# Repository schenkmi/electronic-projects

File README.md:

# electronic-projects
misc electronic projects

# History

## 2026.09.19

### pre-amp-ECC86/kicad/psu-v6
Large PCB PSU for ECC86 with high side switch. Support LT3080 and LM317. Fix Drain/Source.

## 2026.09.02

### pre-amp-ECC86/kicad/psu-v5
Large PCB PSU for ECC86 with high side switch. Support LT3080 and LM317

## 2026.08.26

### pre-amp-ECC86/kicad/psu-v4
Large PCB PSU for ECC86 without relais. Support LT3080 and LM317

## 2026.08.23

### input-sel-attenuator/software/v9
Power up timer to 64ms wait till voltage is stabilized

## 2026.08.10

### pre-amp-ECC86/kicad/psu-v3
Large PCB PSU for ECC86

## 2026.08.01

### pre-amp-ECC86/kicad/psu-v2
Shrinked and optimized PSU for ECC86

## 2026.07.22

### pre-amp-ECC86/kicad/psu-v1
First version of PSU for ECC86 

## 2026.07.12

### pre-amp-ECC86/kicad/v1
First version of ECC86 based pre-amplifier

### spdif-recv-ak4118-ak4137/software/spdif-recv-ak4118-ak4137-v4.X
Updated software for V4 PCB

## 2026.06.05

### dac-pcm1702-v1/kicad-psu-v8/
DC/DC for +5V digital path

### dac-pcm1702-v1/kicad-asrc-v14
PCB LED fix
External LED support

### spdif-recv-ak4118-ak4137/kicad/v4
External LED support
Change one LDO to TLV1117-3.3 due to power dissipation

## 2026.05.28

### dac-pcm1702-v1/kicad-asrc-v13
PCB re-design with fixed LED ordering

## 2026.05.27

### pre-amp-26A7/ltspice/v2/
New CCS simulation with smaller FETs

## 2026.05.26

### dac-pcm1702-v1/software/spdif-recv-asrc-4392-v12.X
New software for SPDIF ASRC receiver including UART and IR

## 2026.05.16

### dac-pcm1702-v1/kicad-asrc-v12
PSU re-design, UART for debugging, I2C debugging, IR

### spdif-recv-ak4118-ak4137/kicad/v3
Add IR support

## 2026.05.10

### spdif-recv-cs8416-ak4137/kicad/v7
Improved power supply, I2S debug, Serial console

### spdif-recv-ak4118-ak4137/kicad/v2
Small redesign

## 2026.04.25

### spdif-recv-ak4118-ak4137/kicad/v1
Finalize and ordered

### pre-amp-26A7/kicad/v2
Finalize and ordered

## 2026.03.29

### pre-amp-26A7/kicad/v1
Finalize and ordered v1

## 2026.03.28

### lv-psu-dcdc/kicad/fixed-v3
Better thermal management for DC/DC

### lv-lownoise-psu/kicad/v7-dcdc-large-cap
Better thermal handling on DC/DC

### input-sel-attenuator/kicad/v9-10k-47k
Changed footprint for L1 and C1

## 2026.03.11

### lv-psu-dcdc/kicad/fixed-v2
Eval board with different inductors

### hv-psu-discrete/kicad/maida-lt3080-v5
HV PSU with DC/DC for +5V output

## 2026.03.05

### lv-lownoise-psu/kicad/v6-dcdc-large-cap
Finalize v6 with large reservoir cap

## 2026.02.25

### hv-psu-discrete/kicad/maida-lt3080-v5-26A7GT
HV PSU for 26A7 pre-amp

## 2026.01.13

### input-sel-attenuator/software/ir-debug-v3
Update MCC generated code

### dac-pcm1792a/software/asrc-pcm1792a-v4.X
Update MCC generated code

### dac-pcm1702-v1/software/v8
Update MCC generated code

### spdif-recv-cs8416-ak4137/software/spdif-recv-cs8416-ak4137-v5.X
Update MCC generated code

### input-sel-attenuator/software/v9
Update MCC generated code

### rpi-hat-spdif/kicad/V9
RPI HAT SPDIF Output increase hole diameter to 3.2mm

### rpi-hat-spdif/kicad/V9-min
RPI HAT SPDIF Output minized PCB increase hole diameter to 3.2mm

## 2026.01.01

### adapter/spdif/kicad/v2
LVDS SPDIF XMIT with rotated connector 

### adapter/spdif/kicad/v2b
LVDS SPDIF XMIT with standard connector 

### rpi-hat-spdif/kicad/V7-min
RPI HAT SPDIF Output minized PCB

### rpi-hat-spdif/kicad/V8
RPI HAT SPDIF Output new PCB

## 2025.12.20

### adapter/spdif/kicad/v1
Finalize v1 LVDS SPDIF XMIT

### rpi-hat-spdif/kicad/v6
RPI HAT SPDIF Output

### rpi-hat-spdif/kicad/v6-min
RPI HAT SPDIF Output minimized

## 2025.12.08

### pre-amp-ECC88/kicad/v9
Finalize and ordered v9

## 2025.09.29

### retro/c64-user-port-led
Finalize v1 of C64 user port LED

## 2025.09.28

### dac-pcm1704/kicad/dac-df1706-pcm1704-v2
Finalize and ordered v2

## 2025.09.21

### dac-pcm1704/kicad/dac-pcm1704-v5
Finalize and ordered v5

### dac-pcm1702-v1/kicad-i2s-nos-v7
Finalize and ordered v7

### dac-pcm1792a/kicad/v6/
Finalize and ordered v6

## 2025.09.13

### input-sel-attenuator/software/ir-debug-v2

### input-sel-attenuator/software/v8
V2.5 2025.09.12 Shiny new push button and saving handling
     Use volume when doing channel switch.

## 2025.09.07

### lv-lownoise-psu/kicad/v5-dcdc
Finalize and ordered v5

### lv-lownoise-psu/kicad/v5-dcdc-large-cap
Finalize and ordered v5 with large reservoir cap

## 2025.08.25

### lt1115-phono-mm-mc/kicad/v6
Finalize and ordered v6

## 2025.08.23

### dac-pcm1702-v1/kicad-psu-v7
Finalize and ordered v7

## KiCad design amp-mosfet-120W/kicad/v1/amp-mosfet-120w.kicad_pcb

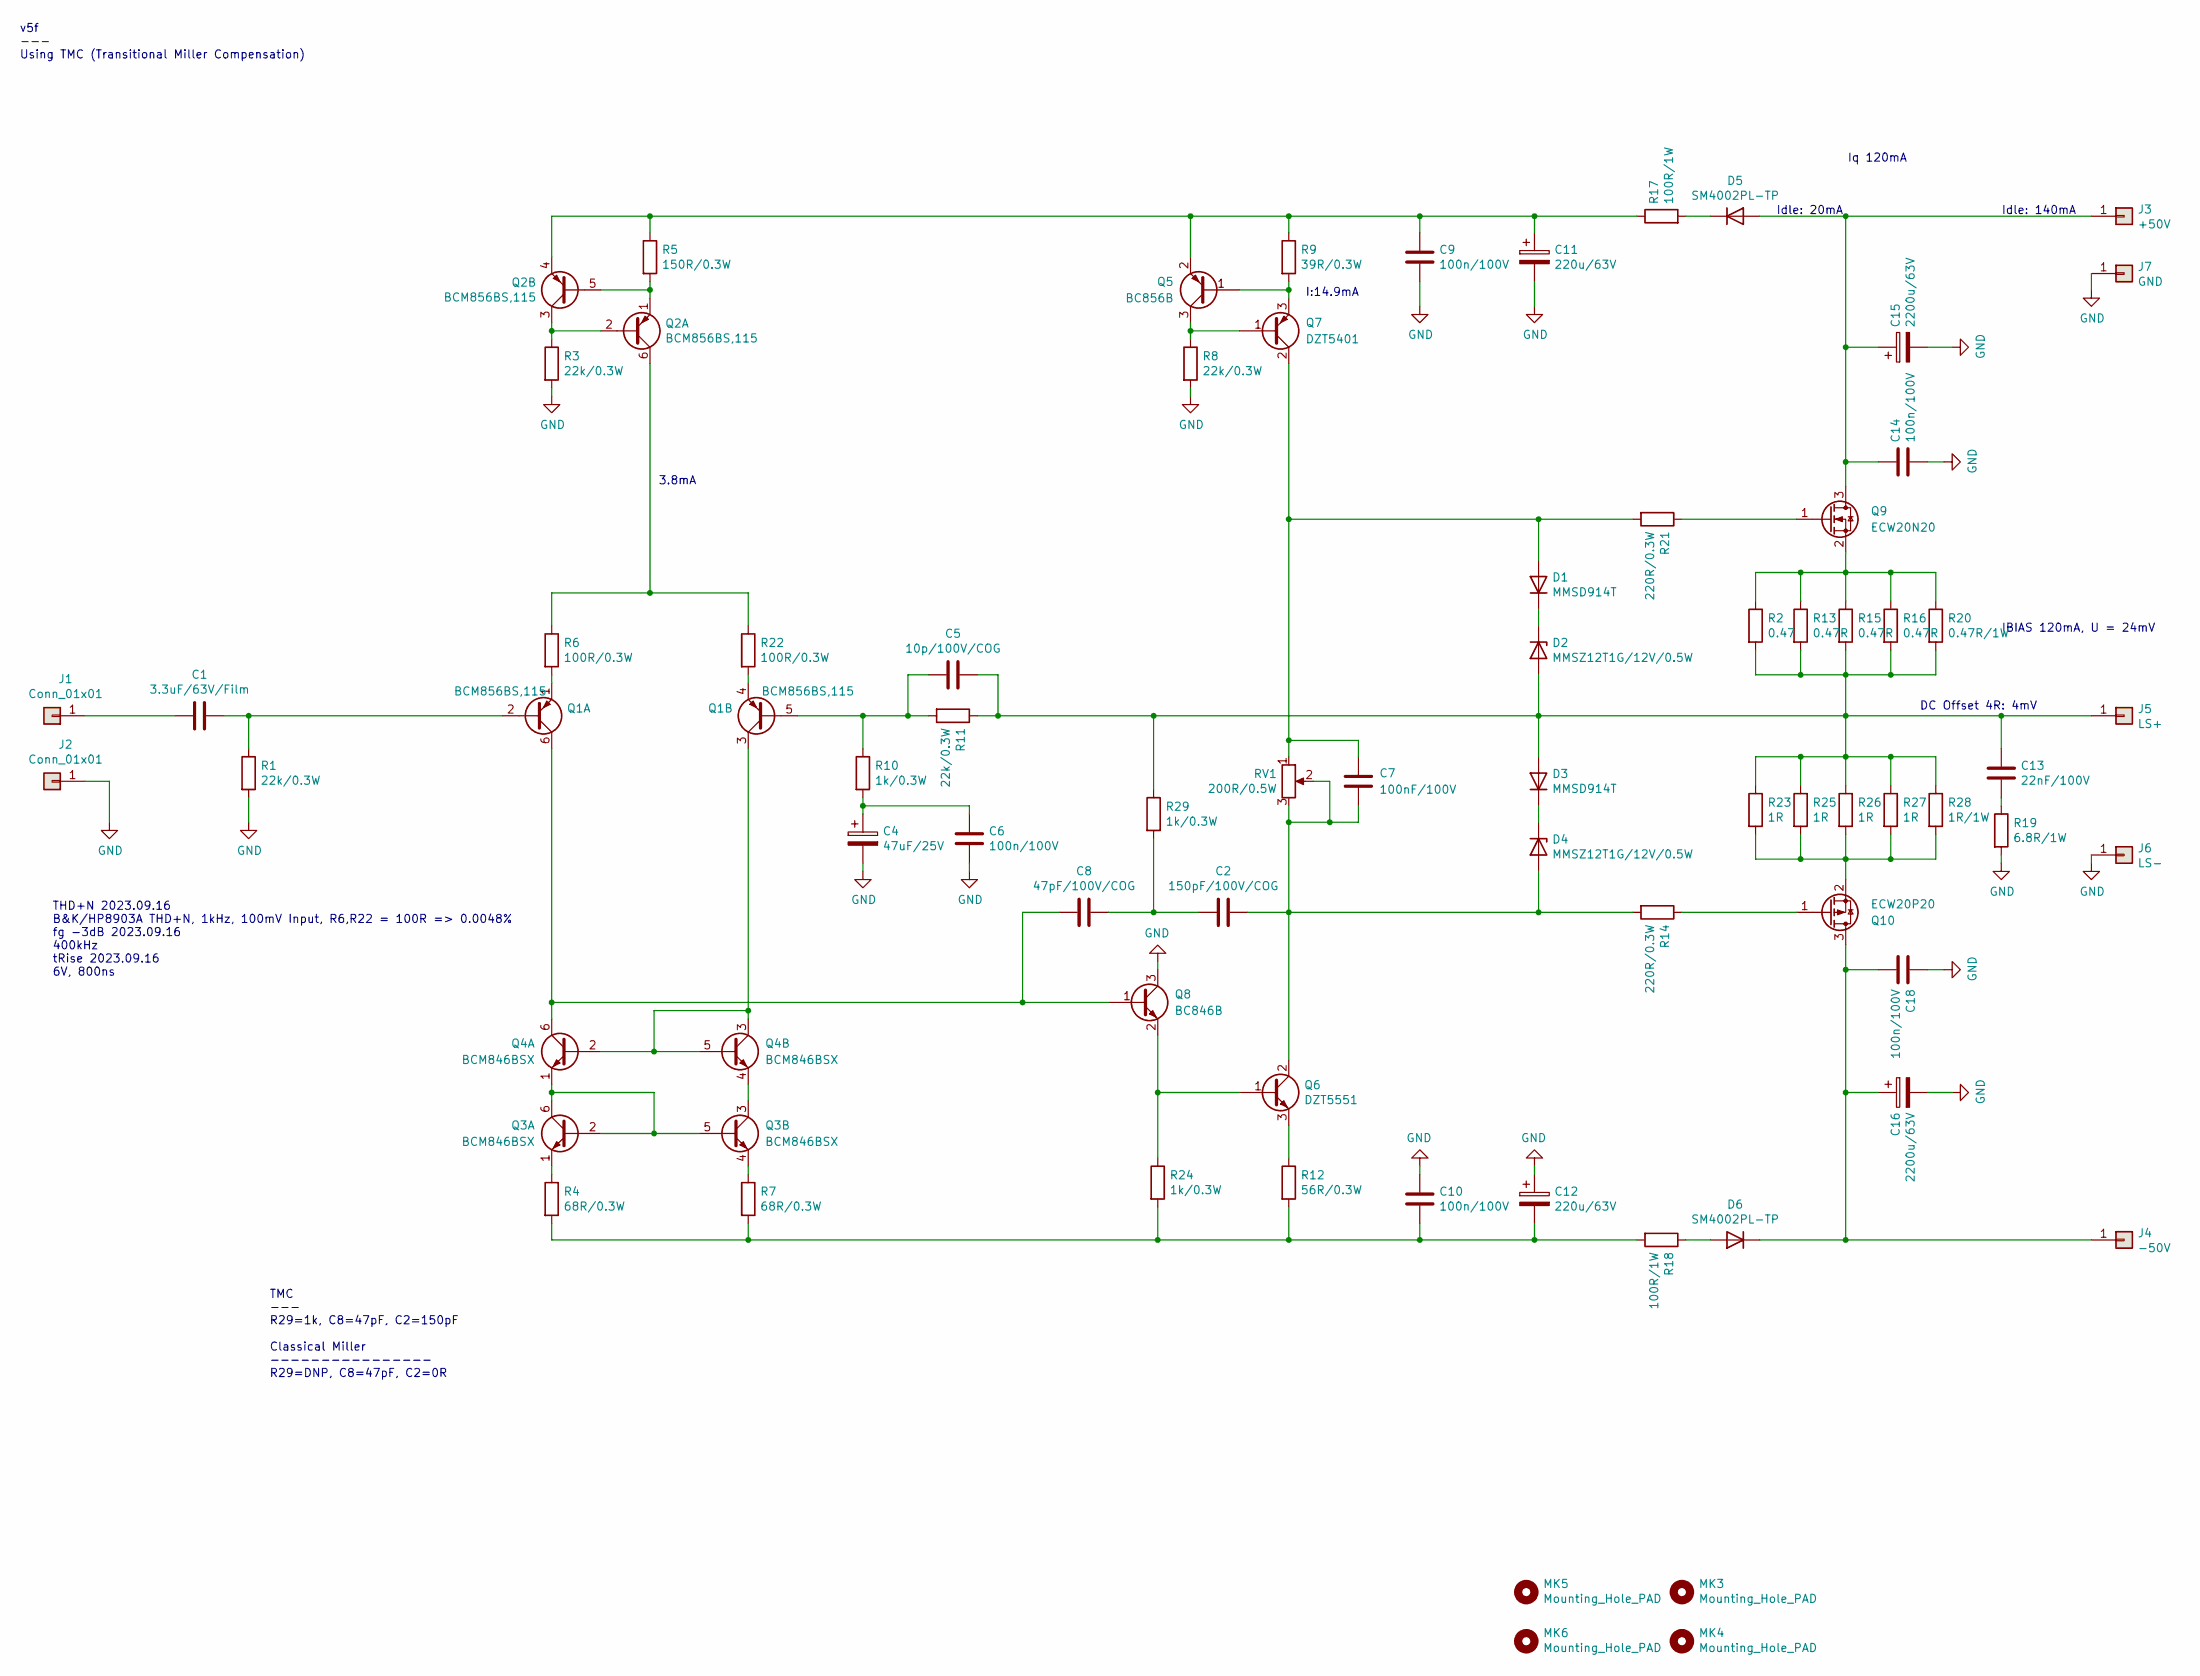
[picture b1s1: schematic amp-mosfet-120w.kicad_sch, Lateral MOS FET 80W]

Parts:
C1: 3.3uF/63V/Film; C_Rect_L7.2mm_W7.2mm_P5.00mm_FKS2_FKP2_MKS2_MKP2
C2: 150pF/100V/COG; C_0805_2012Metric_Pad1.18x1.45mm_HandSolder
C4: 47uF/25V; CP_Radial_D5.0mm_P2.00mm
C5: 10p/100V/COG; C_0805_2012Metric_Pad1.18x1.45mm_HandSolder
C6, C9, C10: 100n/100V; C_Rect_L7.2mm_W2.5mm_P5.00mm_FKS2_FKP2_MKS2_MKP2
C7: 100nF/100V; C_Rect_L7.2mm_W2.5mm_P5.00mm_FKS2_FKP2_MKS2_MKP2
C8: 47pF/100V/COG; C_0805_2012Metric_Pad1.18x1.45mm_HandSolder
C11, C12: 220u/63V; CP_Radial_D12.5mm_P5.00mm
C13: 22nF/100V; C_Rect_L7.2mm_W2.5mm_P5.00mm_FKS2_FKP2_MKS2_MKP2
C14, C18: 100n/100V; C_1206_3216Metric_Pad1.33x1.80mm_HandSolder
C15, C16: 2200u/63V; CP_Radial_D18.0mm_P7.50mm
D1, D3: MMSD914T; D_SOD-123
D2, D4: MMSZ12T1G/12V/0.5W; D_SOD-123
D5, D6: SM4002PL-TP; D_SOD-123F
J1, J2: Conn_01x01; Pin_D1.0mm_L10.0mm
J3: +50V; TE-726386-2_Pitch5.08mm_Drill1.3mm
J4: -50V; TE-726386-2_Pitch5.08mm_Drill1.3mm
J5: LS+; TE-726386-2_Pitch5.08mm_Drill1.3mm
J6: LS-; TE-726386-2_Pitch5.08mm_Drill1.3mm
J7: GND; TE-726386-2_Pitch5.08mm_Drill1.3mm
MK3, MK4: Mounting_Hole_PAD; MountingHole_3.2mm_M3_Pad_Via
MK5, MK6: Mounting_Hole_PAD; MountingHole_3.2mm_M3
Q1, Q2: BCM856BS,115; SOT-363_SC-70-6
Q3, Q4: BCM846BSX; SOT-363_SC-70-6
Q5: BC856B; SOT-23
Q6: DZT5551; SOT-223-3_TabPin2
Q7: DZT5401; SOT-223-3_TabPin2
Q8: BC846B; SOT-23
Q9: ECW20N20; TO-264-3_Horizontal_TabDown
Q10: ECW20P20; TO-264-3_Horizontal_TabDown
R1, R3, R8, R11: 22k/0.3W; R_0805_2012Metric_Pad1.20x1.40mm_HandSolder
R2: 0.47; R_MELF_MMB-0207
R4, R7: 68R/0.3W; R_0805_2012Metric_Pad1.20x1.40mm_HandSolder
R5: 150R/0.3W; R_0805_2012Metric_Pad1.20x1.40mm_HandSolder
R6, R22: 100R/0.3W; R_0805_2012Metric_Pad1.20x1.40mm_HandSolder
R9: 39R/0.3W; R_0805_2012Metric_Pad1.20x1.40mm_HandSolder
R10, R24, R29: 1k/0.3W; R_0805_2012Metric_Pad1.20x1.40mm_HandSolder
R12: 56R/0.3W; R_0805_2012Metric_Pad1.20x1.40mm_HandSolder
R13, R15, R16: 0.47R; R_MELF_MMB-0207
R14, R21: 220R/0.3W; R_0805_2012Metric_Pad1.20x1.40mm_HandSolder
R17, R18: 100R/1W; R_MELF_MMB-0207
R19: 6.8R/1W; R_MELF_MMB-0207
R20: 0.47R/1W; R_MELF_MMB-0207
R23, R25, R26, R27: 1R; R_MELF_MMB-0207
R28: 1R/1W; R_MELF_MMB-0207
RV1: 200R/0.5W; Potentiometer_Bourns_3296W_Vertical

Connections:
GND: C4.2, C6.2, C9.2, C10.1, C11.2, C12.1, C14.2, C15.2, C16.2, C18.1, J2.1 (Pin_1_1), J6.1 (Pin_1_1), J7.1 (Pin_1_1), Q8.3 (C), R1.2, R3.2, R8.2, R19.2
unnamed: C2.2, C8.1, R29.2
unnamed: C4.1, C6.1, R10.2
unnamed: C10.2, C12.2, R4.2, R7.2, R12.2, R18.2, R24.2
unnamed: C13.2, R19.1
unnamed: C7.2, D1.2 (A), Q7.2 (C), R21.2, RV1.1
unnamed: D1.1 (K), D2.1 (K)
unnamed: C5.1, C13.1, D2.2 (A), D3.2 (A), J5.1 (Pin_1_1), R2.2, R11.1, R13.2, R15.2, R16.2, R20.2, R23.1, R25.1, R26.1, R27.1, R28.1, R29.1
unnamed: D3.1 (K), D4.1 (K)
unnamed: C2.1, C7.1, D4.2 (A), Q6.2 (C), R14.2, RV1.2, RV1.3
unnamed: C14.1, C15.1, D5.2 (A), J3.1 (Pin_1_1), Q9.3 (D)
unnamed: D5.1 (K), R17.2
unnamed: D6.2 (A), R18.1
unnamed: C16.1, C18.2, D6.1 (K), J4.1 (Pin_1_1), Q10.3 (D)
unnamed: C1.2, J1.1 (Pin_1_1)
unnamed: C1.1, Q1.2 (B1), R1.1
unnamed: C8.2, Q1.6 (C1), Q4.6 (C1), Q8.1 (B)
unnamed: Q1.1 (E1), R6.2
unnamed: C5.2, Q1.5 (B2), R10.1, R11.2
unnamed: Q1.3 (C2), Q4.2 (B1), Q4.3 (C2), Q4.5 (B2)
unnamed: Q1.4 (E2), R22.2
unnamed: Q2.2 (B1), Q2.3 (C2), R3.1
unnamed: Q2.6 (C1), R6.1, R22.1
unnamed: Q2.1 (E1), Q2.5 (B2), R5.2
unnamed: C9.1, C11.1, Q2.4 (E2), Q5.2 (E), R5.1, R9.1, R17.1
unnamed: Q3.2 (B1), Q3.5 (B2), Q3.6 (C1), Q4.1 (E1)
unnamed: Q3.1 (E1), R4.1
unnamed: Q3.3 (C2), Q4.4 (E2)
unnamed: Q3.4 (E2), R7.1
unnamed: Q5.1 (B), Q7.3 (E), R9.2
unnamed: Q5.3 (C), Q7.1 (B), R8.1
unnamed: Q6.1 (B), Q8.2 (E), R24.1
unnamed: Q6.3 (E), R12.1
unnamed: Q9.1 (G), R21.1
unnamed: Q9.2 (S), R2.1, R13.1, R15.1, R16.1, R20.1
unnamed: Q10.1 (G), R14.1
unnamed: Q10.2 (S), R23.2, R25.2, R26.2, R27.2, R28.2

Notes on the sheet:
THD+N 2023.09.16 B&K/HP8903A THD+N, 1kHz, 100mV Input, R6,R22 = 100R => 0.0048% fg -3dB 2023.09.16 400kHz tRise 2023.09.16 6V, 800ns
TMC --- R29=1k, C8=47pF, C2=150pF Classical Miller ---------------- R29=DNP, C8=47pF, C2=0R
Iq 120mA
Idle: 20mA
v5f --- Using TMC (Transitional Miller Compensation)
Idle: 140mA
DC Offset 4R: 4mV
3.8mA
I:14.9mA
IBIAS 120mA, U = 24mV

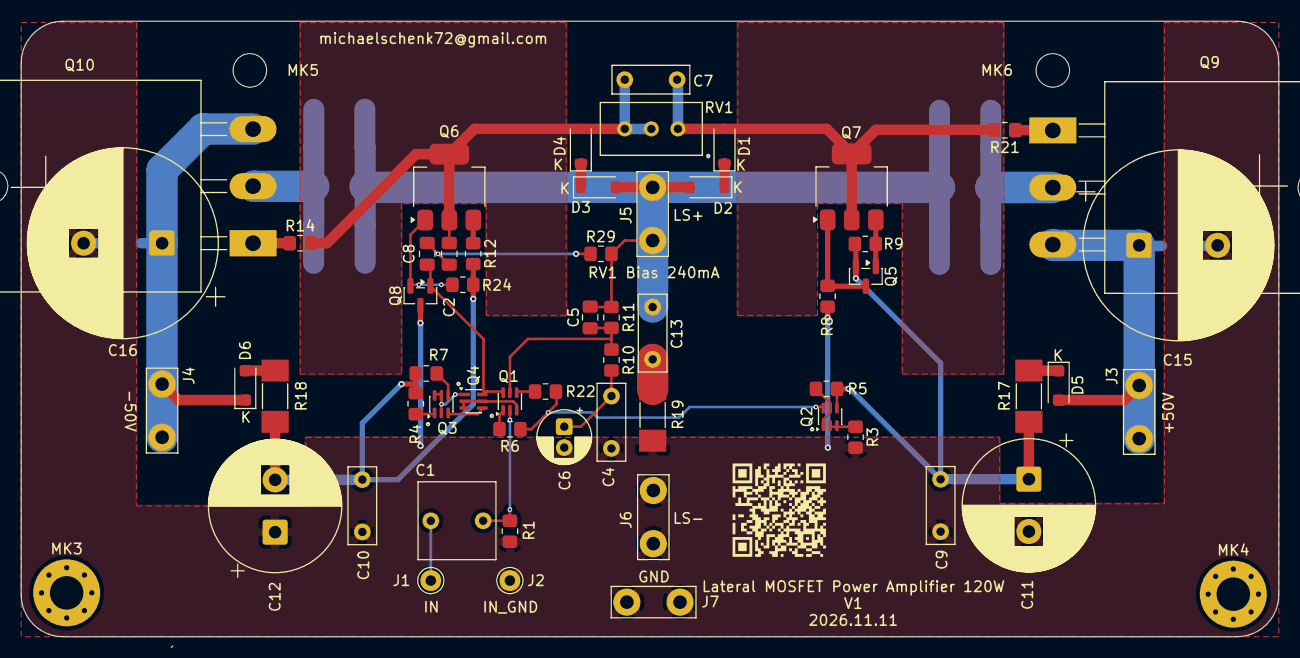
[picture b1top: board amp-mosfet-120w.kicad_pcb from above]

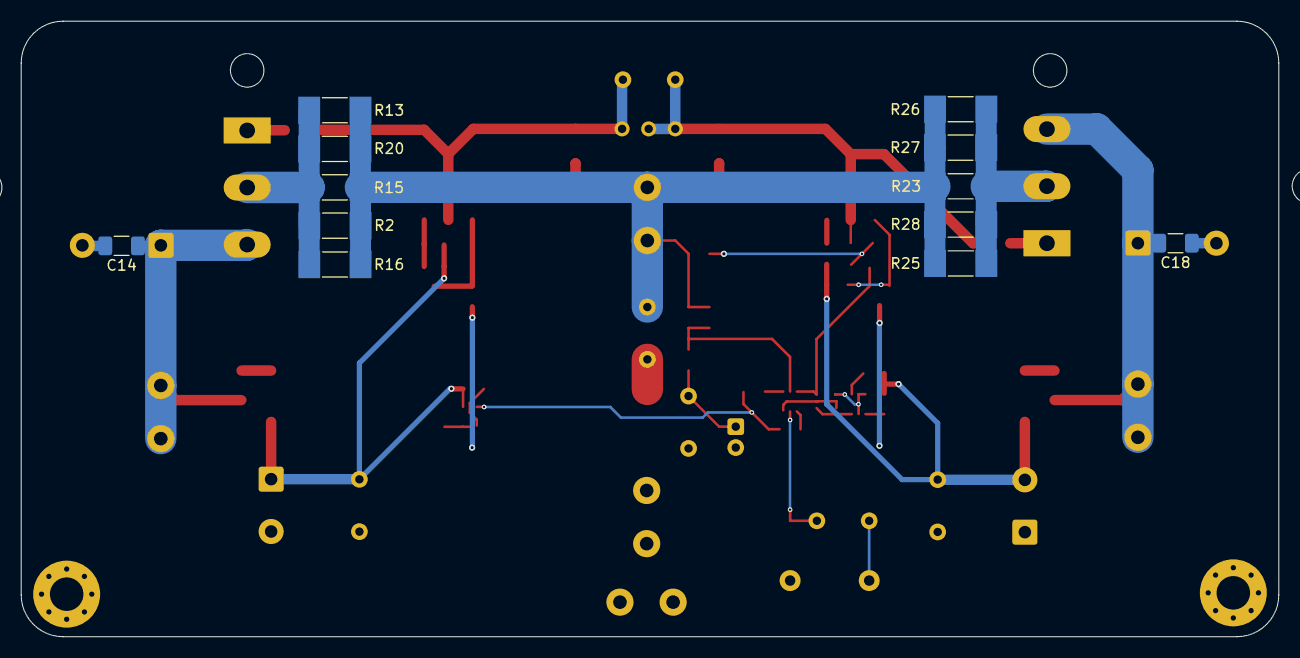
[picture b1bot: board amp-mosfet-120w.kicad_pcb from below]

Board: 2 copper layers, 120.1 x 58.8 mm, 73 parts (12 on the bottom side), 37 nets.

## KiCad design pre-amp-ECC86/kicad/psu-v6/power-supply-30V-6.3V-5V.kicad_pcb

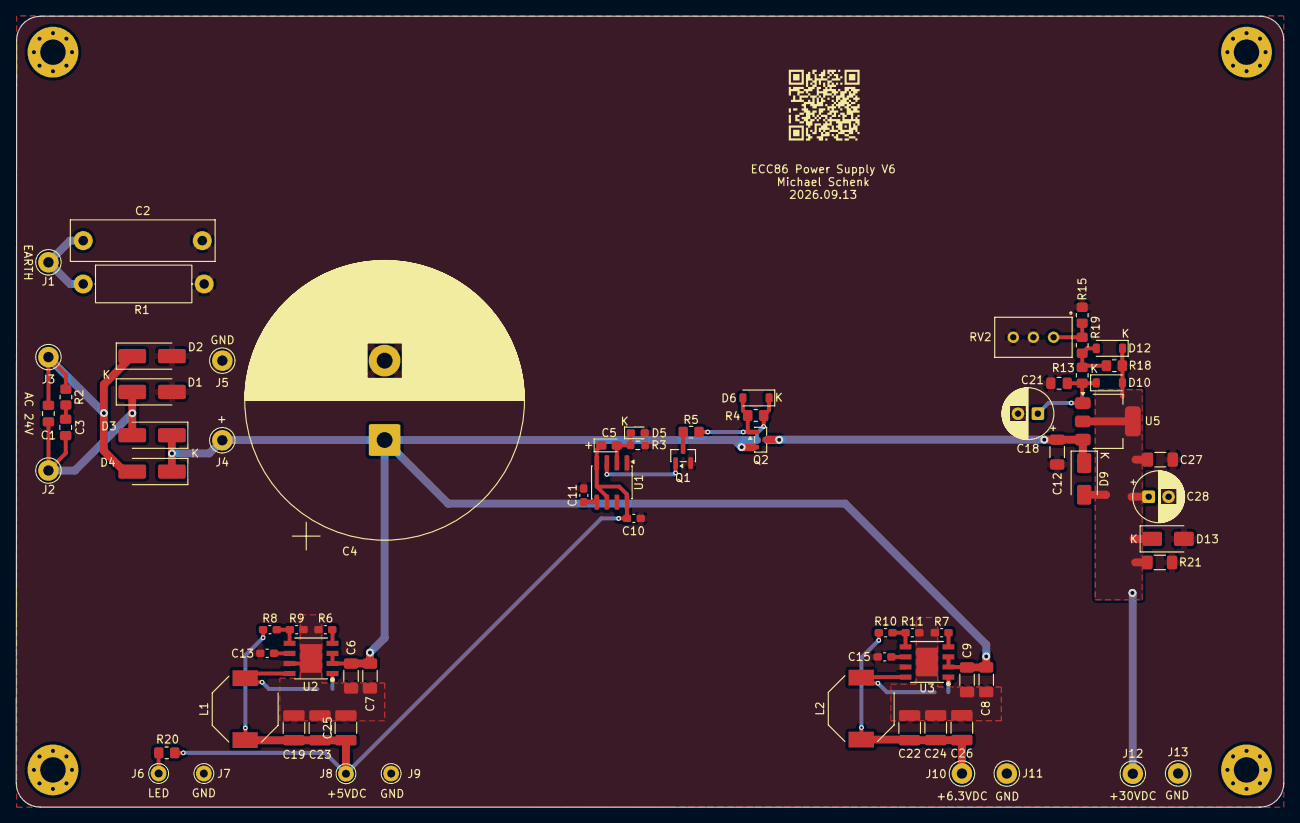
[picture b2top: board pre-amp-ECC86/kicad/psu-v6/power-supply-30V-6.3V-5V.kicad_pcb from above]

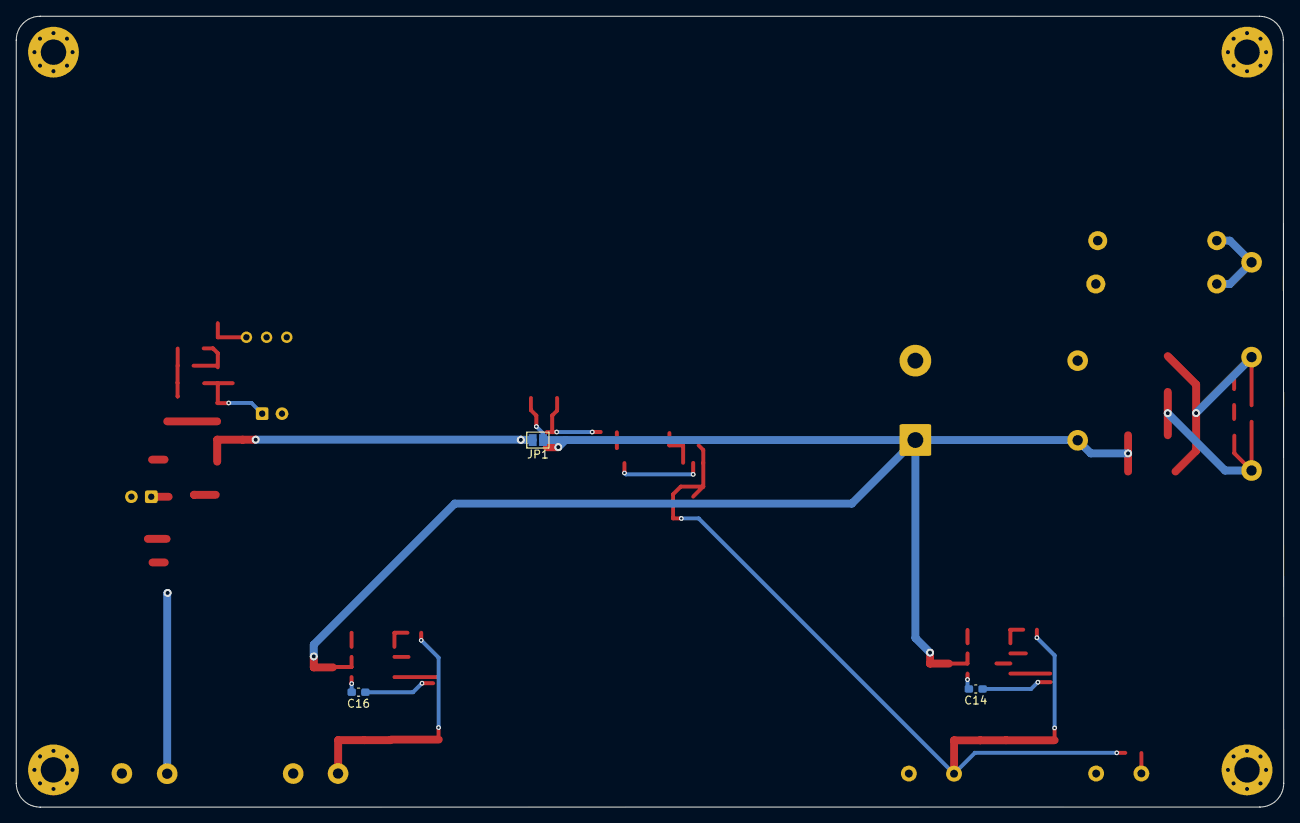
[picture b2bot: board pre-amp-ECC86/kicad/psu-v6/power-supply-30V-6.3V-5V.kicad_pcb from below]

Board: 2 copper layers, 159.7 x 99.6 mm, 80 parts (3 on the bottom side), 29 nets.

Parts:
C1: Cx/10nF/50V; C_0805_2012Metric_Pad1.18x1.45mm_HandSolder
C2: 2.2nF 2kV; C_Rect_L18.0mm_W5.0mm_P15.00mm_FKS3_FKP3
C3: Cs/50V; C_0805_2012Metric_Pad1.18x1.45mm_HandSolder
C4: 10000uF/50V; CP_Radial_D35.0mm_P10.00mm_SnapIn
C5: 15uF/6.3V; CP_EIA-2012-12_Kemet-R_HandSolder
C6, C7, C8, C9, C12: 10uF/50V/X7R; C_1206_3216Metric_Pad1.33x1.80mm_HandSolder
C10, C11: 100nF/50V; C_0603_1608Metric_Pad1.08x0.95mm_HandSolder
C13: 10nF/50V; C_0603_1608Metric_Pad1.08x0.95mm_HandSolder
C14, C16: 100nF/50V/X7R; C_0603_1608Metric_Pad1.08x0.95mm_HandSolder
C15: 4.7uF/10V; C_0603_1608Metric_Pad1.08x0.95mm_HandSolder
C18: 10uF/50V; CP_Radial_D6.3mm_P2.50mm
C19, C22, C23, C24, C25, C26: 22uF/25V/X7R; C_1210_3225Metric_Pad1.33x2.70mm_HandSolder
C21: 10nF/100V/C0G; C_0805_2012Metric_Pad1.18x1.45mm_HandSolder
C27: 100nF/50V/COG; C_1206_3216Metric_Pad1.33x1.80mm_HandSolder
C28: 47uF/50V; CP_Radial_D6.3mm_P2.50mm
D1, D2, D3, D4: BYG22B-E3; D_SMA_Handsoldering
D5: TS4148RCG; D_0603_1608Metric_Pad1.05x0.95mm_HandSolder
D6: BZT52B12; D_SOD-123
D9: SS110; D_SMA
D10, D12: BAT46W; D_SOD-123
D13: S1M; D_SMA
H1, H2, H3, H4: MountingHole; MountingHole_3.2mm_M3_Pad_Via
J1: EARTH; Pin_D1.3mm_L11.0mm
J2, J3: AC-LV; Pin_D1.3mm_L11.0mm
J4: IN; Pin_D1.3mm_L11.0mm
J5, J11, J13: GND; Pin_D1.3mm_L11.0mm
J6: LED; Pin_D1.0mm_L10.0mm
J7, J9: GND; Pin_D1.0mm_L10.0mm
J8: +5V; Pin_D1.0mm_L10.0mm
J10: LV; Pin_D1.3mm_L11.0mm
J12: HV; Pin_D1.3mm_L11.0mm
JP1: SolderJumper_2_Open; SolderJumper-2_P1.3mm_Open_Pad1.0x1.5mm
L1, L2: 15uH; L_Bourns-SRU8028_8.0x8.0mm
Q1: MMBTRC116SS; SOT-23
Q2: SL2309; SOT-23
R1: 100R/2W; R_Axial_DIN0414_L11.9mm_D4.5mm_P15.24mm_Horizontal
R2: Rs/1/8W; R_0805_2012Metric_Pad1.20x1.40mm_HandSolder
R3: 1Meg; R_0603_1608Metric_Pad0.98x0.95mm_HandSolder
R4: 100k; R_0805_2012Metric_Pad1.20x1.40mm_HandSolder
R5: 22k; R_0805_2012Metric_Pad1.20x1.40mm_HandSolder
R6, R7: 100k; C_0603_1608Metric_Pad1.08x0.95mm_HandSolder
R8: 52.3k; C_0603_1608Metric_Pad1.08x0.95mm_HandSolder
R9, R11: 10k; C_0603_1608Metric_Pad1.08x0.95mm_HandSolder
R10: 69.8k; C_0603_1608Metric_Pad1.08x0.95mm_HandSolder
R13: 49.9k; R_0805_2012Metric_Pad1.20x1.40mm_HandSolder
R15, R19: 24.9k; R_0805_2012Metric_Pad1.20x1.40mm_HandSolder
R18: 499R; R_0805_2012Metric_Pad1.20x1.40mm_HandSolder
R20: 330R; R_0805_2012Metric_Pad1.20x1.40mm_HandSolder
R21: 30k/0.25W; R_1206_3216Metric_Pad1.30x1.75mm_HandSolder
RV2: 50k; Potentiometer_Bourns_3296W_Vertical
U1: TLC555xD; SOIC-8_3.9x4.9mm_P1.27mm
U2, U3: AP64202QSP-13; Diodes_PSOP-8
U5: LT3080xST; SOT-223

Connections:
+5V: C5.1, C10.1, C19.1, C23.1, C25.1, J8.1 (Pin_1_1), L1.2, R8.1, R20.2, U1.4 (~RST), U1.6 (THRES), U1.8 (VCC)
/HV: C27.1, C28.1, D9.2 (A), D10.2 (A), D12.1 (K), D13.1 (K), J12.1 (Pin_1_1), R18.2, R21.2, U5.2 (OUT), U5.4 (OUT)
GND: C2.2, C4.2, C6.1, C7.2, C8.1, C9.2, C10.2, C11.2, C12.2, C13.2, C15.2, C18.2, C19.2, C21.2, C22.2, C23.2, C24.2, C25.2, C26.2, C27.2, C28.2, D1.2 (A), D2.2 (A), D5.2 (A), D13.2 (A), J5.1 (Pin_1_1), J7.1 (Pin_1_1), J9.1 (Pin_1_1), J11.1 (Pin_1_1), J13.1 (Pin_1_1), Q1.2 (E), R1.2, R3.2, R6.2, R7.2, R9.2, R11.2, R15.1, R21.1, RV2.2, RV2.3, U1.1 (GND), U2.7 (GND), U2.9 (EP), U3.7 (GND), U3.9 (EP)
HS-SW: Q1.1 (B), U1.3 (OUT)
unnamed: C3.2, R2.1
unnamed: C1.1, C3.1, D1.1 (K), D3.2 (A), J2.1 (Pin_1_1)
unnamed: C1.2, D2.1 (K), D4.2 (A), J3.1 (Pin_1_1), R2.2
unnamed: C4.1, C6.2, C7.1, C8.2, C9.1, D3.1 (K), D4.1 (K), D6.1 (K), J4.1 (Pin_1_1), JP1.1 (A), Q2.2 (S), R4.2, U2.2 (IN), U2.3 (EN), U3.2 (IN), U3.3 (EN)
unnamed: C5.2, D5.1 (K), R3.1, U1.2 (TRIG)
unnamed: D6.2 (A), Q2.1 (G), R4.1, R5.1
unnamed: C12.1, D9.1 (K), JP1.2 (B), Q2.3 (D), U5.3 (IN)
unnamed: C18.1, C21.1, D10.1 (K), R13.2, U5.1 (SET)
unnamed: D12.2 (A), R13.1, R18.1, R19.2
unnamed: C2.1, J1.1 (Pin_1_1), R1.1
unnamed: J6.1 (Pin_1_1), R20.1
unnamed: C22.1, C24.1, C26.1, J10.1 (Pin_1_1), L2.2, R10.1
unnamed: Q1.3 (C), R5.2
unnamed: R15.2, R19.1, RV2.1
unnamed: C11.1, U1.5 (CONT)
unnamed: C14.2, U2.1 (BST)
unnamed: R8.2, R9.1, U2.5 (FB)
unnamed: R6.1, U2.4 (RT/CLK)
unnamed: C13.1, U2.6 (SS)
unnamed: C14.1, L1.1, U2.8 (SW)
unnamed: C16.2, U3.1 (BST)
unnamed: R10.2, R11.1, U3.5 (FB)
unnamed: R7.1, U3.4 (RT/CLK)
unnamed: C15.1, U3.6 (SS)
unnamed: C16.1, L2.1, U3.8 (SW)

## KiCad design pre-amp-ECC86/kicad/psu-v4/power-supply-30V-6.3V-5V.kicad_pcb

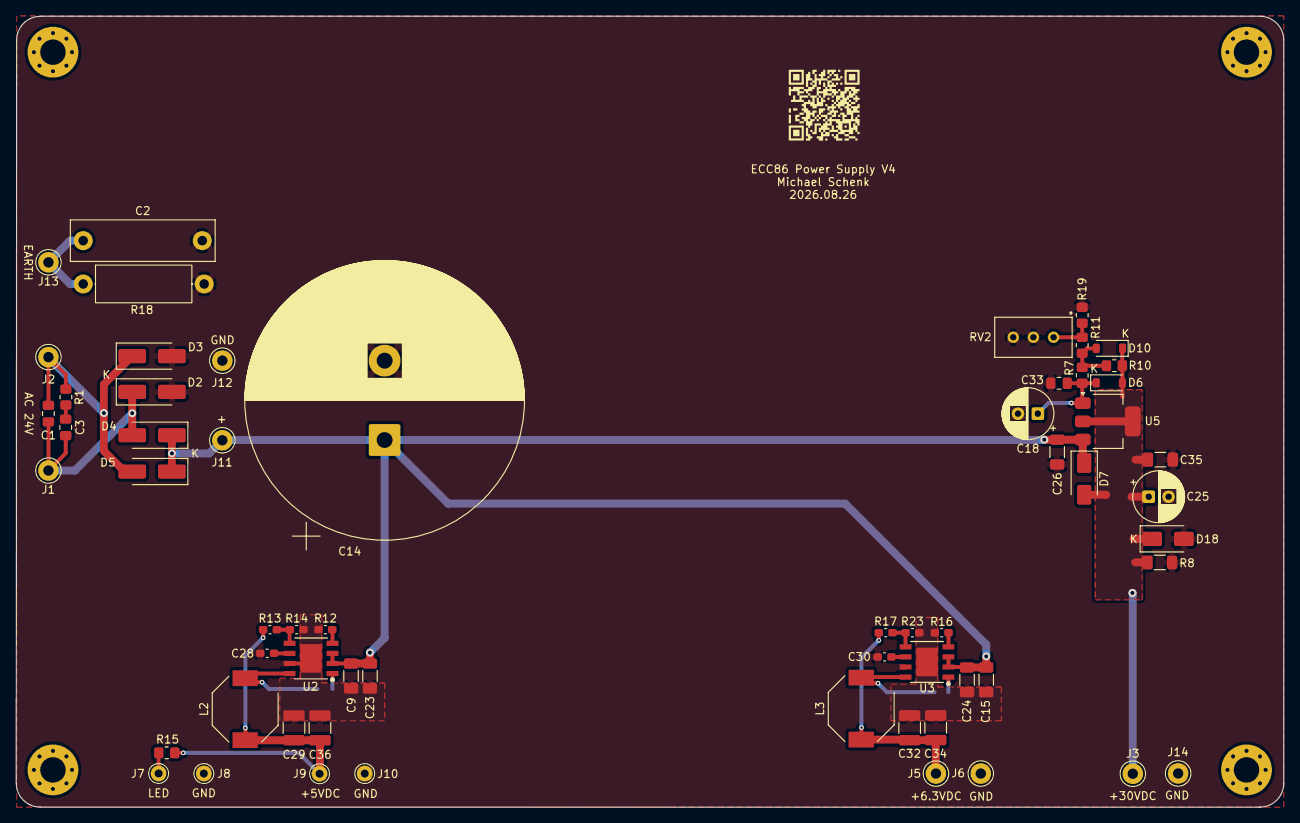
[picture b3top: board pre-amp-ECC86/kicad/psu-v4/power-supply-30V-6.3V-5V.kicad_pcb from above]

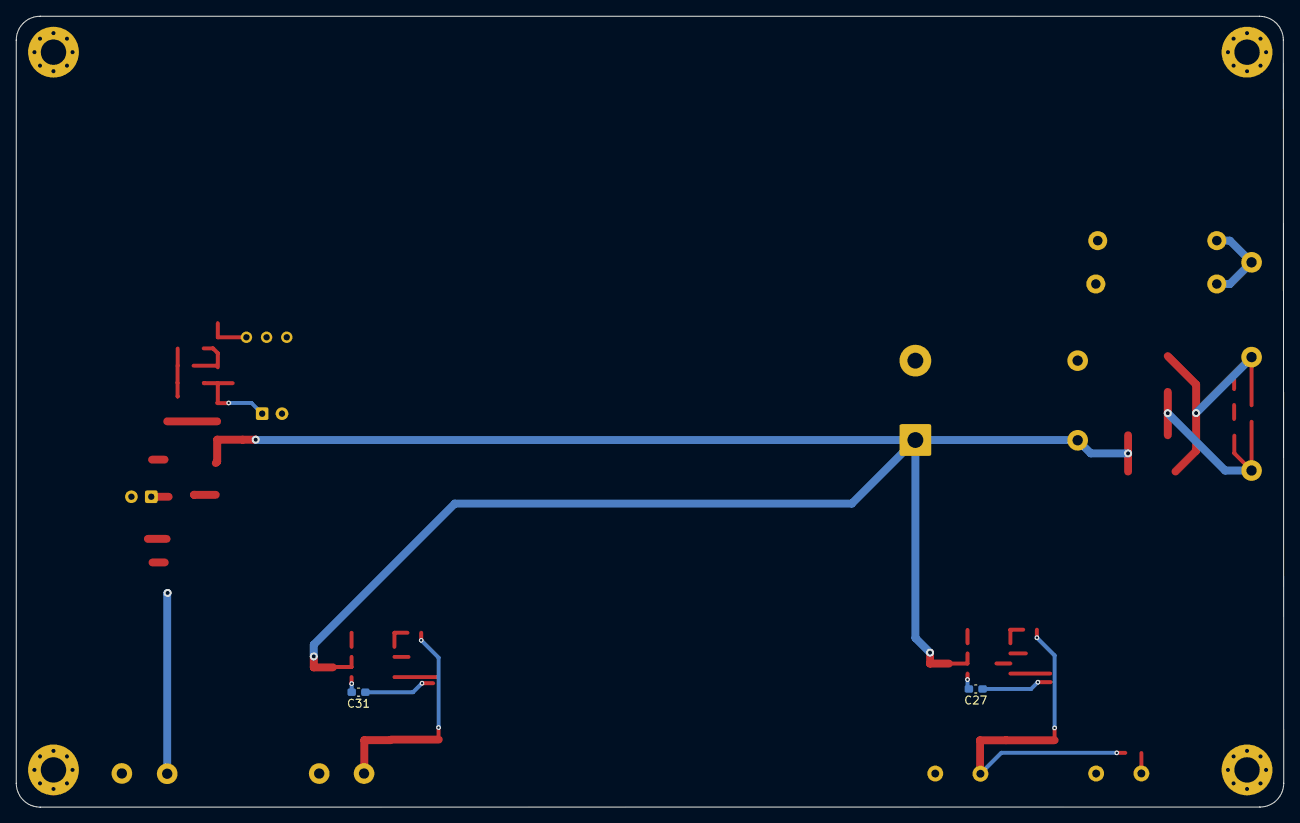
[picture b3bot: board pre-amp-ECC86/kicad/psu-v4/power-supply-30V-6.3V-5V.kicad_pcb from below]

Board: 2 copper layers, 159.7 x 99.6 mm, 66 parts (2 on the bottom side), 23 nets.

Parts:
C1: Cx/10nF/50V; C_0805_2012Metric_Pad1.18x1.45mm_HandSolder
C2: 2.2nF 2kV; C_Rect_L18.0mm_W5.0mm_P15.00mm_FKS3_FKP3
C3: Cs/50V; C_0805_2012Metric_Pad1.18x1.45mm_HandSolder
C9, C15, C23, C24, C26: 10uF/50V/X7R; C_1206_3216Metric_Pad1.33x1.80mm_HandSolder
C14: 10000uF/50V; CP_Radial_D35.0mm_P10.00mm_SnapIn
C18: 10uF/50V; CP_Radial_D6.3mm_P2.50mm
C25: 47uF/50V; CP_Radial_D6.3mm_P2.50mm
C27, C31: 100nF/50V/X7R; C_0603_1608Metric_Pad1.08x0.95mm_HandSolder
C28: 10nF/50V; C_0603_1608Metric_Pad1.08x0.95mm_HandSolder
C29, C32, C34, C36: 22uF/25V/X7R; C_1210_3225Metric_Pad1.33x2.70mm_HandSolder
C30: 4.7uF/10V; C_0603_1608Metric_Pad1.08x0.95mm_HandSolder
C33: 10nF/100V/C0G; C_0805_2012Metric_Pad1.18x1.45mm_HandSolder
C35: 100nF/50V/COG; C_1206_3216Metric_Pad1.33x1.80mm_HandSolder
D2, D3, D4, D5: BYG22B-E3; D_SMA_Handsoldering
D6, D10: BAT46W; D_SOD-123
D7: SS110; D_SMA
D18: S1M; D_SMA
H1, H2, H3, H4: MountingHole; MountingHole_3.2mm_M3_Pad_Via
J1, J2: AC-LV; Pin_D1.3mm_L11.0mm
J3: HV; Pin_D1.3mm_L11.0mm
J5: LV; Pin_D1.3mm_L11.0mm
J6, J12, J14: GND; Pin_D1.3mm_L11.0mm
J7: LED; Pin_D1.0mm_L10.0mm
J8, J10: GND; Pin_D1.0mm_L10.0mm
J9: +5V; Pin_D1.0mm_L10.0mm
J11: IN; Pin_D1.3mm_L11.0mm
J13: EARTH; Pin_D1.3mm_L11.0mm
L2, L3: 15uH; L_Bourns-SRU8028_8.0x8.0mm
R1: Rs/1/8W; R_0805_2012Metric_Pad1.20x1.40mm_HandSolder
R7: 49.9k; R_0805_2012Metric_Pad1.20x1.40mm_HandSolder
R8: 30k/0.25W; R_1206_3216Metric_Pad1.30x1.75mm_HandSolder
R10: 499R; R_0805_2012Metric_Pad1.20x1.40mm_HandSolder
R11, R19: 24.9k; R_0805_2012Metric_Pad1.20x1.40mm_HandSolder
R12, R16: 100k; C_0603_1608Metric_Pad1.08x0.95mm_HandSolder
R13: 52.3k; C_0603_1608Metric_Pad1.08x0.95mm_HandSolder
R14, R23: 10k; C_0603_1608Metric_Pad1.08x0.95mm_HandSolder
R15: 330R; R_0805_2012Metric_Pad1.20x1.40mm_HandSolder
R17: 69.8k; C_0603_1608Metric_Pad1.08x0.95mm_HandSolder
R18: 100R/2W; R_Axial_DIN0414_L11.9mm_D4.5mm_P15.24mm_Horizontal
RV2: 50k; Potentiometer_Bourns_3296W_Vertical
U2, U3: AP64202QSP-13; Diodes_PSOP-8
U5: LT3080xST; SOT-223

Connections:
/HV: C25.1, C35.1, D6.2 (A), D7.2 (A), D10.1 (K), D18.1 (K), J3.1 (Pin_1_1), R8.2, R10.2, U5.2 (OUT), U5.4 (OUT)
GND: C2.2, C9.1, C14.2, C15.1, C18.2, C23.2, C24.2, C25.2, C26.2, C28.2, C29.2, C30.2, C32.2, C33.2, C34.2, C35.2, C36.2, D2.2 (A), D3.2 (A), D18.2 (A), J6.1 (Pin_1_1), J8.1 (Pin_1_1), J10.1 (Pin_1_1), J12.1 (Pin_1_1), J14.1 (Pin_1_1), R8.1, R12.2, R14.2, R16.2, R18.2, R19.1, R23.2, RV2.2, RV2.3, U2.7 (GND), U2.9 (EP), U3.7 (GND), U3.9 (EP)
unnamed: C3.2, R1.1
unnamed: C1.1, C3.1, D2.1 (K), D4.2 (A), J1.1 (Pin_1_1)
unnamed: C1.2, D3.1 (K), D5.2 (A), J2.1 (Pin_1_1), R1.2
unnamed: C9.2, C14.1, C15.2, C23.1, C24.1, C26.1, D4.1 (K), D5.1 (K), D7.1 (K), J11.1 (Pin_1_1), U2.2 (IN), U2.3 (EN), U3.2 (IN), U3.3 (EN), U5.3 (IN)
unnamed: C18.1, C33.1, D6.1 (K), R7.2, U5.1 (SET)
unnamed: D10.2 (A), R7.1, R10.1, R11.2
unnamed: C32.1, C34.1, J5.1 (Pin_1_1), L3.2, R17.1
unnamed: J7.1 (Pin_1_1), R15.1
unnamed: C29.1, C36.1, J9.1 (Pin_1_1), L2.2, R13.1, R15.2
unnamed: C2.1, J13.1 (Pin_1_1), R18.1
unnamed: R11.1, R19.2, RV2.1
unnamed: C27.2, U2.1 (BST)
unnamed: R13.2, R14.1, U2.5 (FB)
unnamed: R12.1, U2.4 (RT/CLK)
unnamed: C28.1, U2.6 (SS)
unnamed: C27.1, L2.1, U2.8 (SW)
unnamed: C31.2, U3.1 (BST)
unnamed: R17.2, R23.1, U3.5 (FB)
unnamed: R16.1, U3.4 (RT/CLK)
unnamed: C30.1, U3.6 (SS)
unnamed: C31.1, L3.1, U3.8 (SW)
